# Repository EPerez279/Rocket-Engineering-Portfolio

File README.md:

# Rocket Engineering Portfolio

This repository documents my engineering contributions to our high school rocketry project. My work focuses on embedded programming, custom PCB design, flight-control systems, and physics-based simulation.
## Projects
### Divinity - Flight Computer

A custom rocket flight computer featuring sensor integration, quaternion-based orientation estimation, PID thrust vector control (TVC), and recovery-control logic.

The directory includes my firmware, KiCad PCB designs, and technical documentation.
### Genesis - Launch-Pad Controller

An ESP32-based launch-pad controller featuring a wireless web interface, four-servo control, and launch-sequence management.

The directory includes the original firmware and custom PCB design files. Genesis was tested on the physical PCB and used during some of our model-rocket launches.
### Rocket Flight Simulator

A Python-based simulation developed to study rocket flight dynamics and control behavior.

The simulator uses mathematical modeling and numerical integration to investigate rocket motion and experimental flight-control strategies.
## My Contributions

I developed the embedded firmware, designed the electronic circuits and PCBs, and programmed the flight simulation.

The rocket's physical airframe and structure was built by my teammate Isaiah Cardenas. Our project was developed with guidance from our teacher, Mr. Joaquin Llanes, who also mentored me in the mathematical work.
## Project Status

The repository contains completed development work alongside experimental features and designs that are still being refined. Some PCB features are not implemented in the corresponding firmware versions.

An autonomous powered landing remains a future goal rather than a completed result.

Additional technical details, dependencies, and development notes are provided in each project's README.

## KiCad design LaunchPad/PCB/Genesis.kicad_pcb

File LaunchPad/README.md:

# Genesis - Launch Pad Control Computer

## Project Overview

Genesis is an ESP32-based launch-pad control computer I developed for our high school rocketry project. I designed the electronics and developed the firmware and wireless web interface to manage the launch-pad mechanisms.

The project combines embedded programming, wireless communication, web development, and electromechanical control.
## How It Works

The ESP32 creates a Wi-Fi access point and hosts a browser-based control interface written in HTML, CSS, and JavaScript.

The firmware includes:

- A countdown and launch-status interface.
- A state machine for managing different stages of the launch sequence.
- Control of four servomotors associated with the launch-pad locking and release mechanism.
- Web-server endpoints for interacting with the controller.
- An ignition-control output.

The interface communicates with the ESP32 through HTTP requests.
## Hardware and Software

### Hardware

I designed the custom Genesis PCB, integrating the ESP32 controller, four servo connections, and a rocket motor igniter connection. The schematic and PCB layout are available in the `PCB` directory.

- Custom launch-pad PCB
- Arduino Nano ESP32
- Four servo connections for the launch-pad
  locking and release mechanism
- Rocket motor igniter connection

### Software and Libraries
- [Arduino-ESP32 Core](https://github.com/espressif/arduino-esp32)
  - WiFi
  - WebServer
  - Wire
- [ESP32Servo](https://github.com/madhephaestus/ESP32Servo)
- [Bootstrap 5.3](https://getbootstrap.com/docs/5.3/)
- HTML, CSS, and JavaScript

## Development and Testing

Genesis was developed and tested on the custom launch-pad PCB and used to operate the launch-pad system during some of our model-rocket launches.

Not every launch shown in the portfolio used Genesis.

The repository contains the original firmware from development and testing. It also includes experimental interface elements, such as a commented-out 3D visualization and unfinished telemetry displays.
## My Contributions

I designed the launch-pad electronics and developed the ESP32 firmware and browser interface.

My work included integrating wireless communication, programming the control system, and developing the interface for interacting with the launch-pad mechanisms.

The project was developed as part of our school rocketry team with teacher guidance.
## Project Status

Genesis is a tested experimental prototype, not a fully safety-validated launch system. The source code documents its implemented functionality and development process.

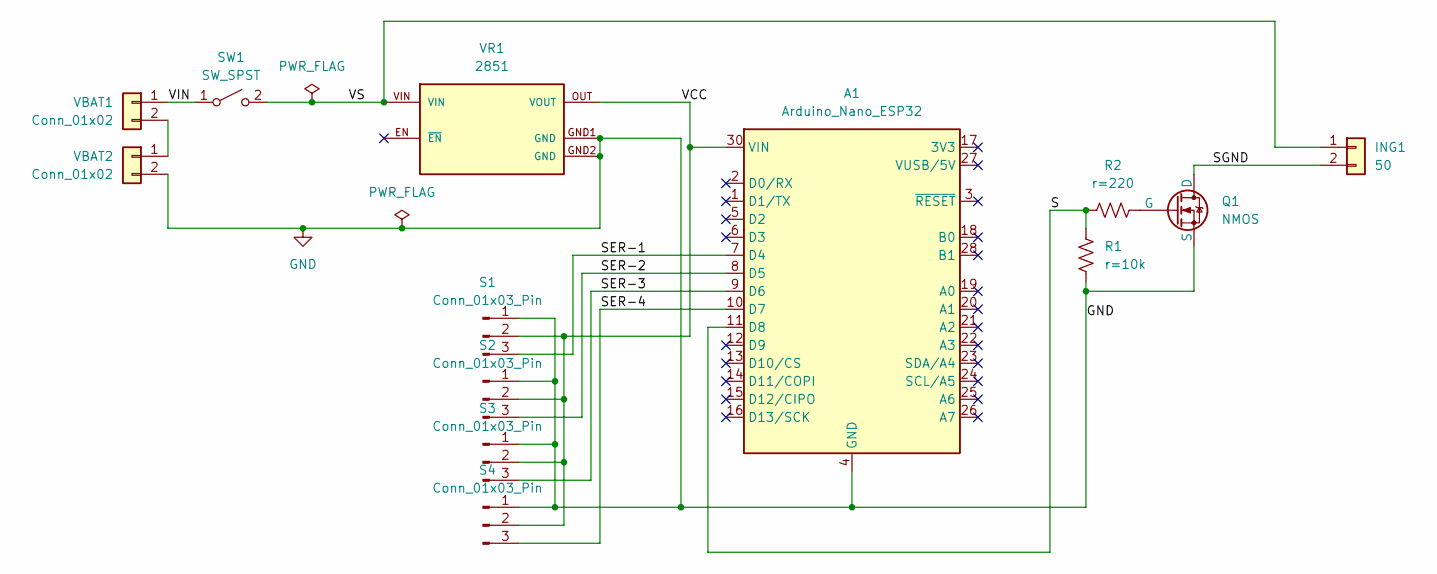
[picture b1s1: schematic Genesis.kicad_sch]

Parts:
A1: Arduino_Nano_ESP32; Arduino_Nano
ING1: 50; TerminalBlock_Phoenix_PT-1,5-2-3.5-H_1x02_P3.50mm_Horizontal
Q1: NMOS; TO-92_Inline_Wide
R1: r=10k; R_Axial_DIN0411_L9.9mm_D3.6mm_P12.70mm_Horizontal
R2: r=220; R_Axial_DIN0411_L9.9mm_D3.6mm_P12.70mm_Horizontal
S1, S2, S3, S4: Conn_01x03_Pin; PinHeader_1x03_P2.54mm_Vertical
SW1: SW_SPST; TerminalBlock_Phoenix_MKDS-1,5-3_1x03_P5.00mm_Horizontal
VBAT1, VBAT2: Conn_01x02; TerminalBlock_Phoenix_PT-1,5-2-3.5-H_1x02_P3.50mm_Horizontal
VR1: 2851; VREG_2851_1; PARTREV 2 January 2018

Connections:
/S: A1.11 (D8), R1.1, R2.1
/SER-1: A1.7 (D4), S1.3
/SER-2: A1.8 (D5), S2.3
/SER-3: A1.9 (D6), S3.3
/SER-4: A1.10 (D7), S4.3
/SGND: ING1.2, Q1.1 (D)
/VCC: A1.30 (VIN), S1.2, S2.2, S3.2, S4.2, VR1.OUT (VOUT)
/VIN: SW1.1 (A), VBAT1.1
/VS: ING1.1, SW1.2 (B), VR1.VIN
GND: A1.4 (GND), A1.29 (GND), Q1.3 (S), R1.2, S1.1, S2.1, S3.1, S4.1, VBAT1.2, VBAT2.1, VBAT2.2, VR1.GND1 (GND), VR1.GND2 (GND)
unnamed: Q1.2 (G), R2.2

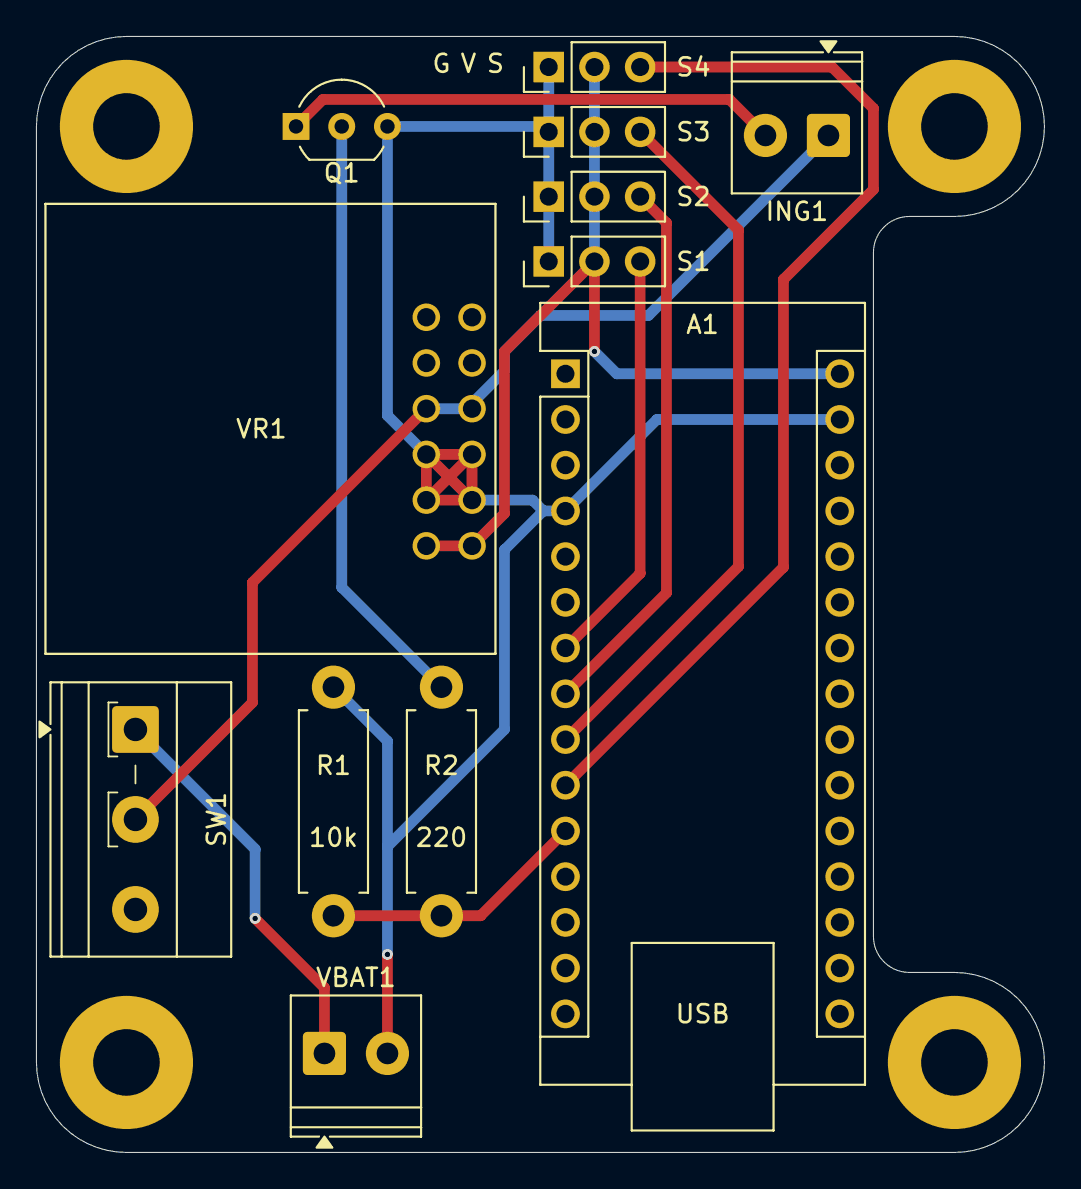
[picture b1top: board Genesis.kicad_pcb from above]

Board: 2 copper layers, 56.0 x 62.0 mm, 12 parts (0 on the bottom side), 11 nets.

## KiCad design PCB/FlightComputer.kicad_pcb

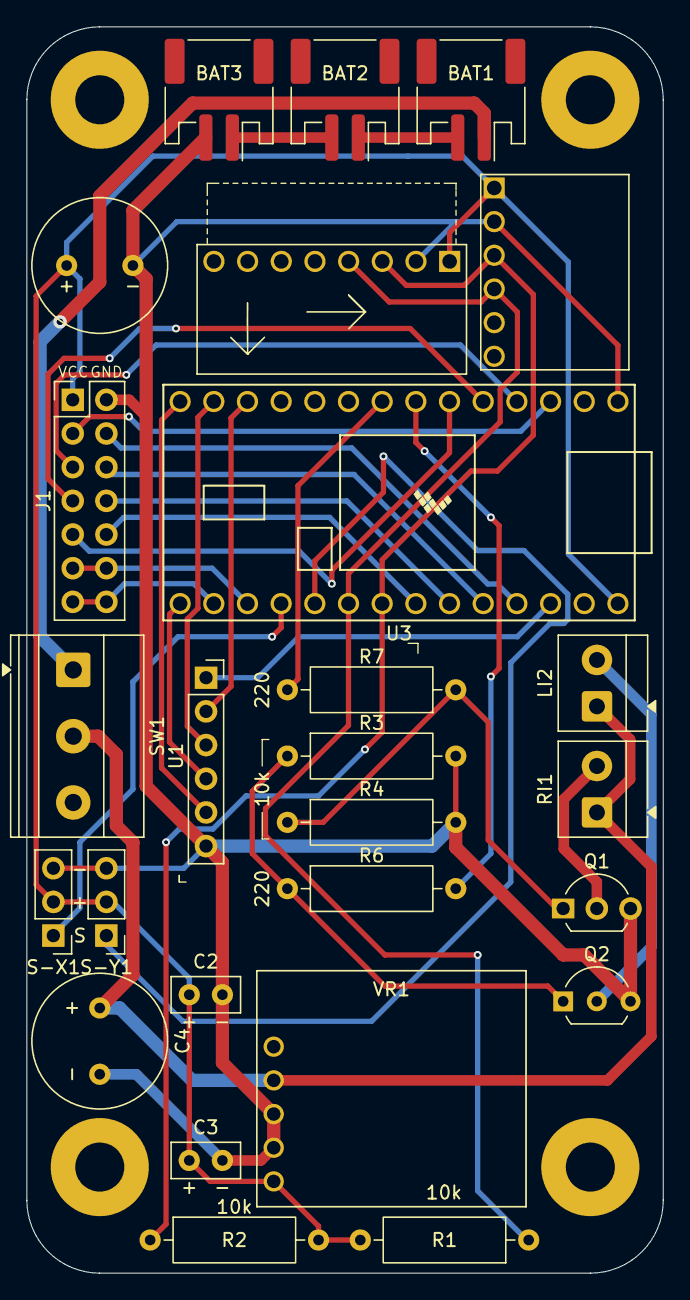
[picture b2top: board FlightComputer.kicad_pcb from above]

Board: 2 copper layers, 48.0 x 94.0 mm, 26 parts (0 on the bottom side), 31 nets.

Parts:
A1: MPU6050_Module
A2: BMP280_Module
BAT1, BAT2, BAT3: 4.7; JST_PH_S2B-PH-SM4-TB_1x02-1MP_P2.00mm_Horizontal
C1: c=2200u; C_Radial_D10.0mm_H12.5mm_P5.00mm
C2, C3: c=0.1u; C_Disc_D5.0mm_W2.5mm_P2.50mm
C4: 2200u; C_Radial_D10.0mm_H12.5mm_P5.00mm
J1: Conn_01x14_Pin; PinHeader_2x07_P2.54mm_Vertical
LI2: r=0.771; TerminalBlock_MetzConnect_Type059_RT06302HBWC_1x02_P3.50mm_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
Q1, Q2: NMOS; TO-92L_Inline_Wide
R1, R2: r=225; R_Axial_DIN0309_L9.0mm_D3.2mm_P12.70mm_Horizontal
R3, R6: R_US; R_Axial_DIN0309_L9.0mm_D3.2mm_P12.70mm_Horizontal
R4: y1=0 y2=3.3 td=0.3 tr=0 tf=0 tw=0.2 per=1; R_Axial_DIN0309_L9.0mm_D3.2mm_P12.70mm_Horizontal
R7: y1=0 y2=3.3 td=0.6 tr=0 tf=0 tw=0.2 per=1; R_Axial_DIN0309_L9.0mm_D3.2mm_P12.70mm_Horizontal
RI1: r=0.771; TerminalBlock_MetzConnect_Type059_RT06302HBWC_1x02_P3.50mm_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
S-X1: Conn_01x03; PinHeader_1x03_P2.54mm_Vertical
S-Y1: Conn_01x03; PinHeader_1x03_P2.54mm_Vertical
SW1: r=1.5; TerminalBlock_Phoenix_MKDS-1,5-3_1x03_P5.00mm_Horizontal
U1: SD_Card_Reader; PinSocket_1x06_P2.54mm_Vertical
U3: Tennsy 4.0; Teensy40
VR1: 2851; VREG_2851

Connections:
/3.3V: U1.1 (+3.3), U3.3.3V_2
/CS: U1.2 (CS), U3.10
/D1: J1.3, U3.1
/D2: J1.5, U3.2
/D3: J1.7, U3.3
/D4: J1.9, U3.4
/D14: J1.13, J1.14, U3.14
/D15: J1.11, J1.12, U3.15
/D20: J1.10, U3.20
/D21: J1.8, U3.21
/D22: J1.6, U3.22
/D23: J1.4, U3.23
/LIQ: Q2.2 (G), R6.1, R7.1
/MISO: U1.5 (MISO), U3.12
/MOSI: U1.3 (MOSI), U3.11
/RIQ: Q1.2 (G), R3.1, R4.1
/S-X: S-X1.1, U3.16
/S-Y: S-Y1.1, U3.17
/SCK: U1.4 (SCK), U3.13
/SCL: A1.3 (SCL), A2.3 (SCL), R2.1, U3.19
/SDA: A1.4 (SDA), A2.4 (SDA), R1.1, U3.18
/V-VG: BAT1.2, BAT2.1
/VB: C4.1, LI2.1, RI1.1, SW1.2 (B), VR1.VIN
/VG-G: BAT2.2, BAT3.1
/VIN: BAT1.1, SW1.1 (A)
GND: A1.2 (GND), A2.2 (GND), BAT3.2, C1.2, C2.2, C3.2, C4.2, J1.2, Q1.3 (S), Q2.3 (S), R4.2, R7.2, S-X1.3, S-Y1.3, U1.6 (GND), U3.G1, VR1.GND1 (GND), VR1.GND2 (GND)
unnamed: LI2.2, Q2.1 (D)
unnamed: Q1.1 (D), RI1.2
unnamed: R3.2, U3.6
unnamed: R6.2, U3.5
VCC: A1.1 (VCC), A2.1 (VCC), C1.1, C2.1, C3.1, J1.1, R1.2, R2.2, S-X1.2, S-Y1.2, U3.VIN, VR1.OUT (VOUT)
